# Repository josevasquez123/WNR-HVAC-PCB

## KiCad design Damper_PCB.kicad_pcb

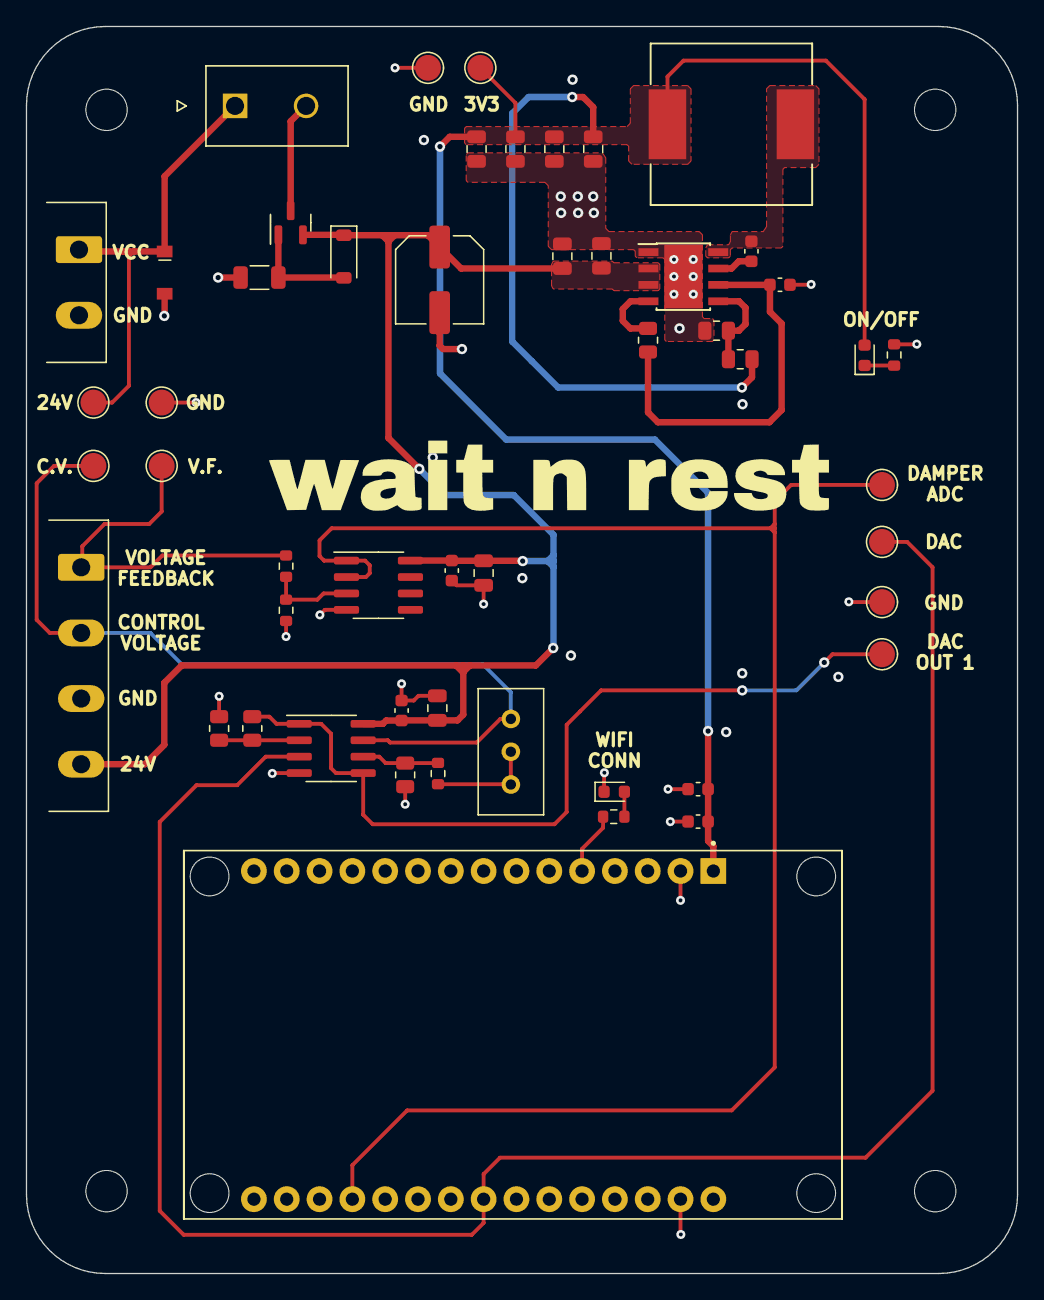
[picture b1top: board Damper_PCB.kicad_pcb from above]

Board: 4 copper layers, 76.7 x 96.5 mm, 55 parts (0 on the bottom side), 23 nets.

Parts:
C100: 22u; C_Elec_6.3x5.4
C101, C202, C204: 10u; C_0805_2012Metric
C102: 220n; C_0805_2012Metric
C103: 1u; C_0603_1608Metric
C104: 0.1u; C_0603_1608Metric
C105, C106, C107, C108: 22u; C_0805_2012Metric
C200, C203, C205: 100n; C_0603_1608Metric
C201: 10u; C_0603_1608Metric
D100: SMF24A-TP; SOD_123FL
D101: MMSZ4697T1G; D_SOD-123
D102, D200: GREEN; LED_0603_1608Metric
H1, H2, H3, H4: MountingHole; MountingHole_3.2mm_M3
J100: VCC INPUT; PhoenixContact_MSTBA_2,5_2-G-5,08_1x02_P5.08mm_Horizontal
J101: SWITCH ON/OFF; MOLEX_39281023
J200: Damper_Conn; PhoenixContact_MSTBA_2,5_4-G-5,08_1x04_P5.08mm_Horizontal
L100: 10u; L_12.3x12.3
Q100: WST4045; SOT-23
R100: 100K; R_1206_3216Metric
R101, R102: 100k; R_0805_2012Metric
R103: 43.2k; R_0805_2012Metric
R104, R200: 1k; R_0603_1608Metric
R201: 15k; R_0805_2012Metric
R202: 10k; R_0805_2012Metric
R203: 10K; R_0805_2012Metric
R204, R205, R206: 1K; R_0603_1608Metric
RV200: 10K; Potentiometer_Bourns_3296W_Vertical
TP100, TP101, TP102, TP103, TP200, TP201, TP202, TP203, TP204, TP205: TestPoint; TestPoint_Pad_D2.0mm
U2, U3: LM358; SOIC-8_3.9x4.9mm_P1.27mm
U100: LMR33620ADDA; Texas_HSOP-8-1EP_3.9x4.9mm_P1.27mm_ThermalVias
U200: ESP32-DEVKIT-V1; MODULE_ESP32_DEVKIT_V1

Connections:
+3V3: C105.2, C106.2, C107.2, C108.2, C200.1, C201.1, D102.2 (A), L100.2, R102.1, TP102.1, U200.1 (3V3)
+24V: C100.1, C101.1, C102.1, C202.2, C203.1, C204.2, C205.1, D101.1 (K), J200.4, Q100.2 (S), U2.8 (V+), U3.8 (V+), U100.2 (VIN), U100.3 (EN)
/MCU_Drivers/DAC: TP201.1, U2.3 (+), U200.23 (D25)
/MCU_Drivers/DAC_OUT_1: R202.2, TP202.1, U2.1, U2.5 (+)
/MCU_Drivers/DAMPER_ADC: TP205.1, U3.1, U3.2 (-), U200.19 (D34)
/MCU_Drivers/DAMPER_CONTROL_VOLTAGE: J200.2, RV200.1, TP203.1, U2.7
/MCU_Drivers/DAMPER_VOLTAGE: J200.1, R205.2, TP204.1
/POWER/V_INPUT: D100.1 (K), J100.1, J101.1, TP101.1
/POWER/switch: J101.2, Q100.3 (D)
GND: C100.2, C101.2, C102.2, C103.1, C105.1, C106.1, C107.1, C108.1, C200.2, C201.2, C202.1, C203.2, C204.1, C205.2, D100.2 (A), D200.1 (K), J100.2, J200.3, R100.2, R103.2, R104.1, R201.1, R203.1, R206.1, TP100.1, TP103.1, TP200.1, U2.4 (V-), U3.4 (V-), U100.1 (PGND), U100.9 (AGND), U200.2 (GND), U200.29 (GND)
unnamed: D101.2 (A), Q100.1 (G), R100.1
unnamed: D102.1 (K), R104.2
unnamed: D200.2 (A), R200.2
unnamed: R204.2, RV200.2, RV200.3
unnamed: R201.2, R202.1, U2.2 (-)
unnamed: R203.2, R204.1, U2.6 (-)
unnamed: R205.1, R206.2, U3.3 (+)
unnamed: C104.2, U100.7 (BOOT)
unnamed: R102.2, R103.1, U100.5 (FB)
unnamed: R101.1, U100.4 (PG)
unnamed: C104.1, L100.1, U100.8 (SW)
unnamed: C103.2, R101.2, U100.6 (VCC)
unnamed: R200.1, U200.5 (D4)

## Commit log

2023-12-20 first version
